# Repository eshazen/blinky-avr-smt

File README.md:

# blinky-avr-smt

## Blinky POV soldering project

This is a soldering practice kit which displays a message in the air
on LEDs when waved back and forth.  

* Programming: https://ohm.bu.edu/~hazen/BlinkyPovAVR/prog/test_prog.html

## Revisions

Revision 5.1 PCB (fall 2023).  See [PCB Documentation](Hardware/avr-smt-44).

* Improve thermal relief on GND/VCC pads
* Change SMT programming connector to thru-hole
* Add pre-programmed message "EPIC"
* Improve error-checking and display on download code
  (blink all LEDs on checksum error)

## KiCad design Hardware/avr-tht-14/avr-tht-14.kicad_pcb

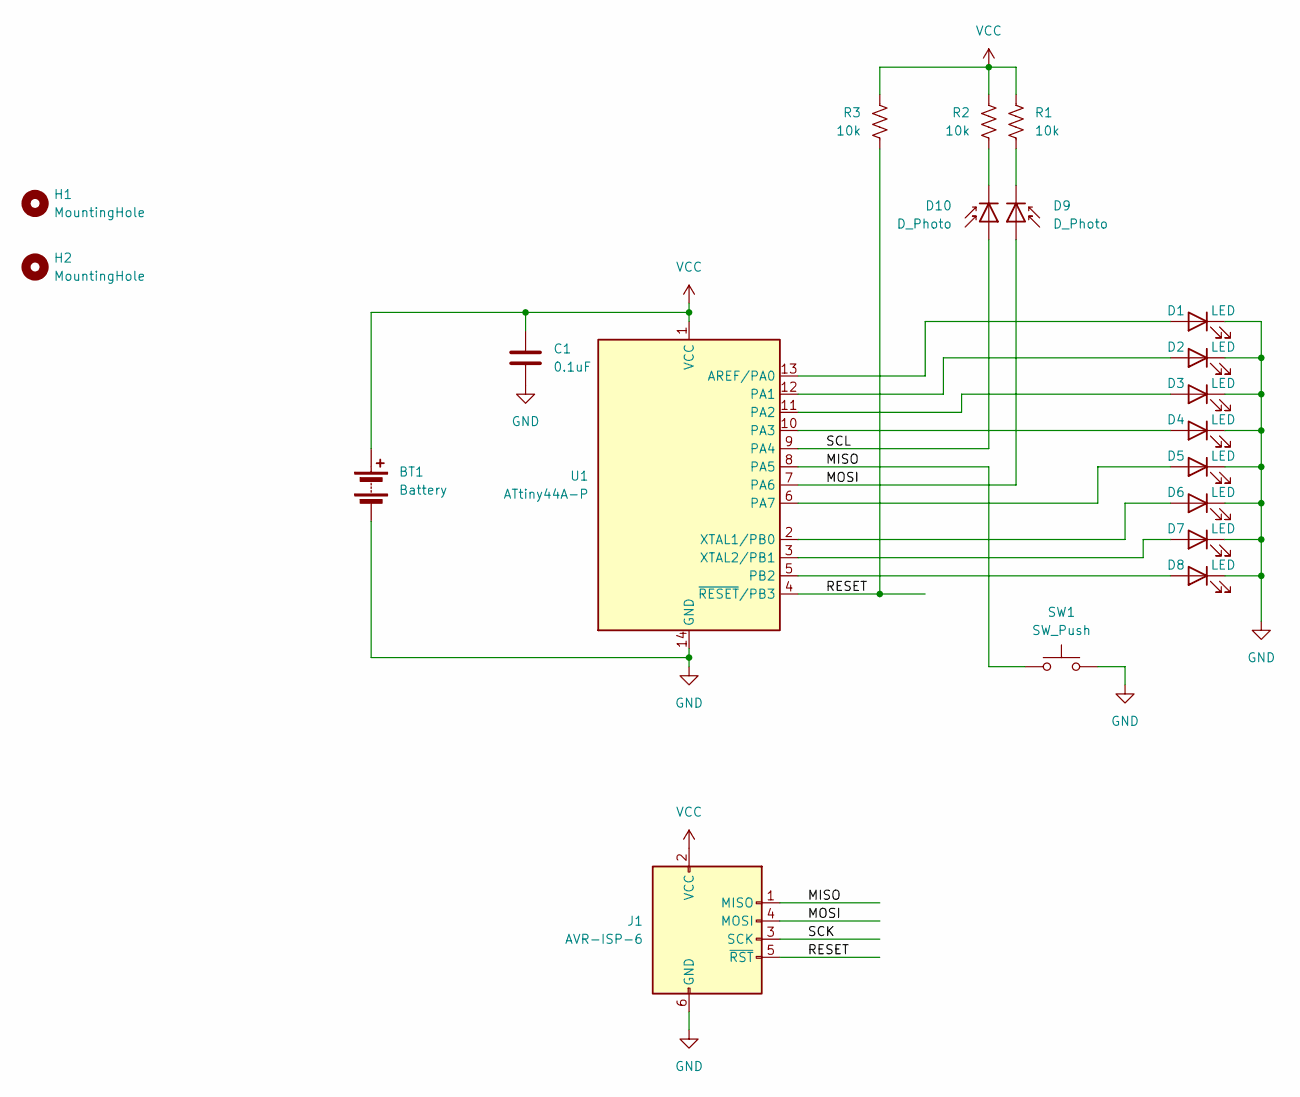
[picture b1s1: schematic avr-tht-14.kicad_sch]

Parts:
BT1: Battery; PinHeader_1x02_P2.54mm_Vertical
C1: 0.1uF; C_Disc_D6.0mm_W2.5mm_P5.00mm
D1, D2, D3, D4, D5, D6, D7, D8: LED; LED_D5.0mm
D9, D10: D_Photo; LED_D3.0mm
H1, H2: MountingHole; MountingHole_4.3mm_M4
J1: AVR-ISP-6; PinHeader_2x03_P2.54mm_Vertical
R1, R2, R3: 10k; R_Axial_DIN0207_L6.3mm_D2.5mm_P10.16mm_Horizontal
SW1: SW_Push; BTN-B3F-1000
U1: ATtiny44A-P; DIP-14_W7.62mm

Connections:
/MISO: J1.1 (MISO), SW1.1, U1.8 (PA5)
/MOSI: D9.2 (A), J1.4 (MOSI), U1.7 (PA6)
/RESET: J1.5 (~RST), R3.2, U1.4 (~RESET/PB3)
/SCK: J1.3 (SCK)
/SCL: D10.2 (A), U1.9 (PA4)
GND: BT1.2 (-), C1.2, D1.1 (K), D2.1 (K), D3.1 (K), D4.1 (K), D5.1 (K), D6.1 (K), D7.1 (K), D8.1 (K), J1.6 (GND), SW1.2, U1.14 (GND)
unnamed: D1.2 (A), U1.13 (AREF/PA0)
unnamed: D2.2 (A), U1.12 (PA1)
unnamed: D3.2 (A), U1.11 (PA2)
unnamed: D4.2 (A), U1.10 (PA3)
unnamed: D5.2 (A), U1.6 (PA7)
unnamed: D6.2 (A), U1.2 (XTAL1/PB0)
unnamed: D7.2 (A), U1.3 (XTAL2/PB1)
unnamed: D8.2 (A), U1.5 (PB2)
unnamed: D9.1 (K), R1.2
unnamed: D10.1 (K), R2.2
VCC: BT1.1 (+), C1.1, J1.2 (VCC), R1.1, R2.1, R3.1, U1.1 (VCC)

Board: 2 copper layers, 20 parts (0 on the bottom side), 16 nets, no tracks yet.

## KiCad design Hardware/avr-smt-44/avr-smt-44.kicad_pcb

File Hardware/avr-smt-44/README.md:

# avr-smt-44

KiCAD design for an SMT version based on ATTiny44/84.
Should be pin/firmware compatible with BlinkyPovAVR4.

## Documentation

* [avr-smt-44.pdf](avr-smt-44.pdf) -- Electrical Schematic
* [avr-smt-44.step](avr-smt-44.step) -- 3D model of assembled board
* [avr-smt-44-Edge_Cuts.pdf](avr-smt-44-Edge_Cuts.pdf) -- Assembly/mechanical drawing
* [avr-smt-44-Edge_Cuts.dxf](avr-smt-44-Edge_Cuts.dxf) -- Assembly/mechanical drawing

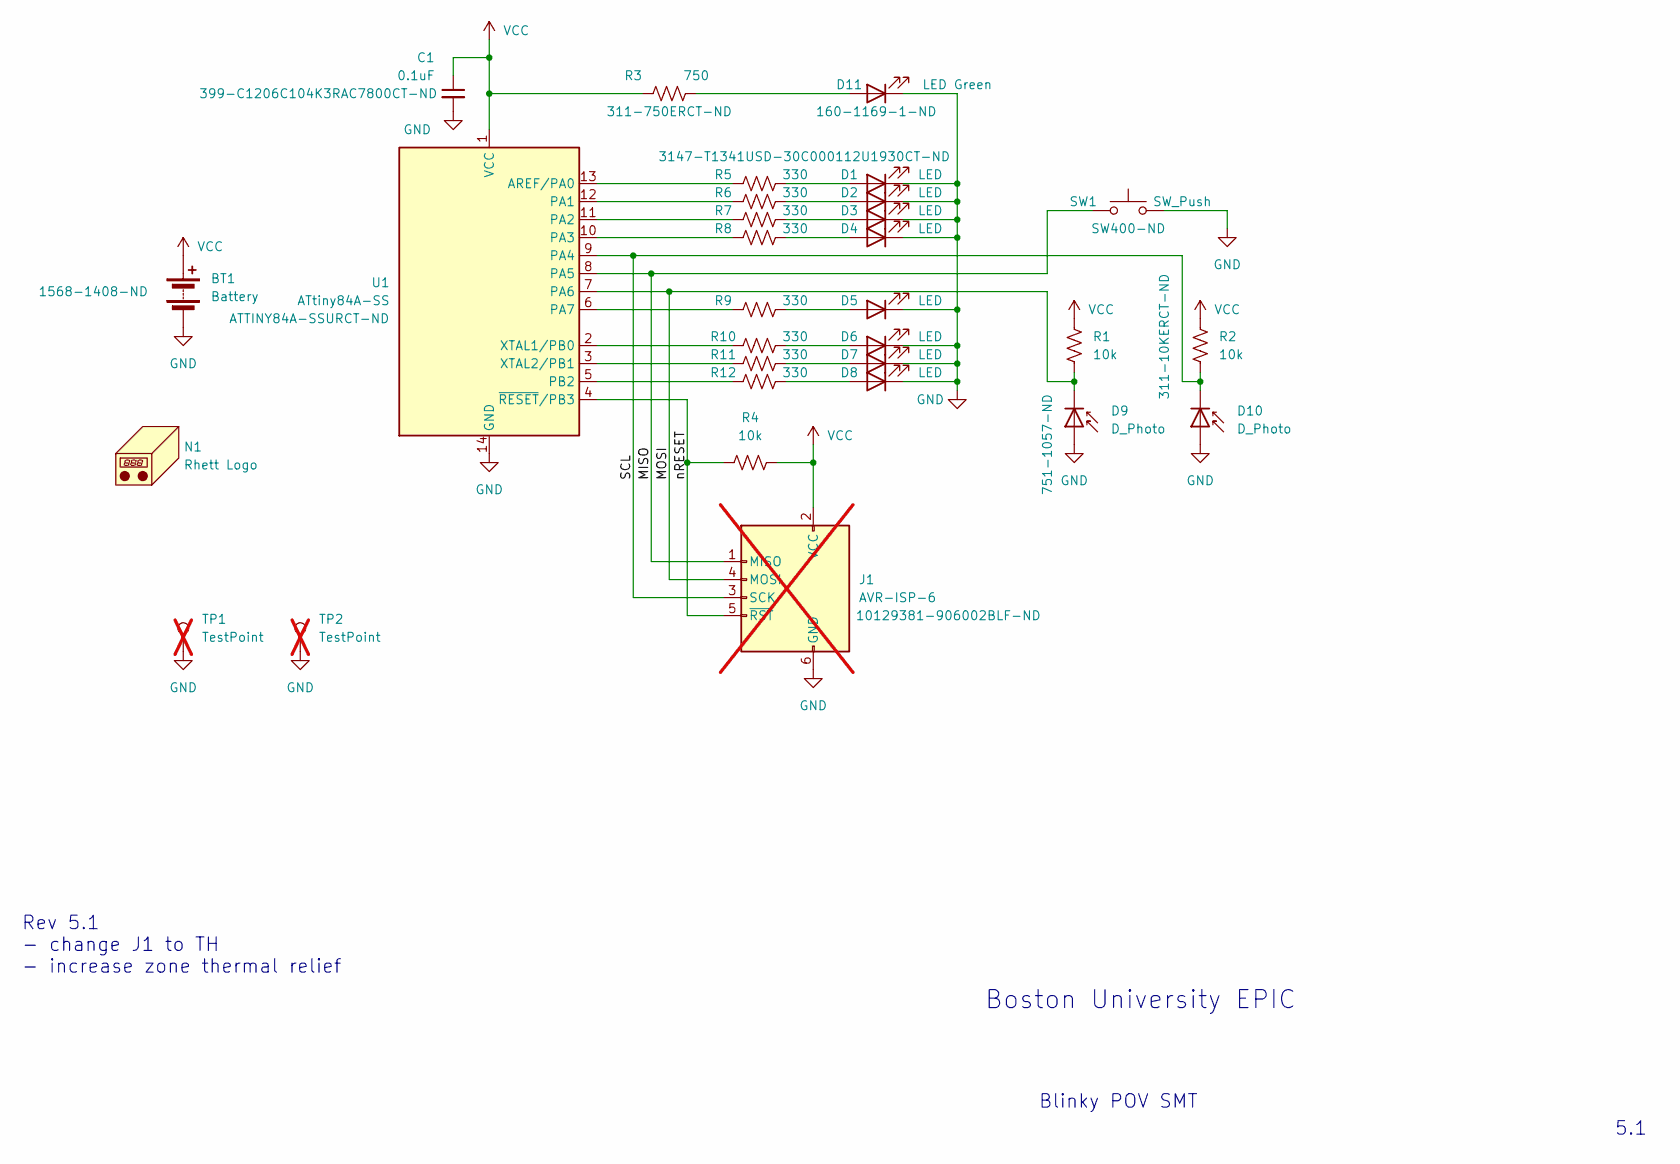
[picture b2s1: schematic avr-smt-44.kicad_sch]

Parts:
BT1: Battery; 2PIN_battery_new2
C1: 0.1uF; C_1206_3216Metric_Pad1.33x1.80mm_HandSolder
D1, D2, D3, D4, D5, D6, D7, D8: LED; LED_1206_3216Metric_Pad1.42x1.75mm_HandSolder
D9, D10: D_Photo; LED_D3.0mm_Horizontal_O3.81mm_Z2.0mm
D11: LED Green; LED_1206_3216Metric_Pad1.42x1.75mm_HandSolder
J1: AVR-ISP-6; PinHeader_2x03_P2.54mm_Vertical; not fitted
N1: Rhett Logo; rhett_logo
R1, R2, R4: 10k; R_1206_3216Metric_Pad1.30x1.75mm_HandSolder
R3: 750; R_1206_3216Metric_Pad1.30x1.75mm_HandSolder
R5, R6, R7, R8, R9, R10, R11, R12: 330; R_1206_3216Metric_Pad1.30x1.75mm_HandSolder
SW1: SW_Push; BTN-B3F-1000
TP1, TP2: TestPoint; TestPoint_Loop_D3.80mm_Drill2.0mm; not fitted
U1: ATtiny84A-SS; SOIC-14_3.9x8.7mm_P1.27mm

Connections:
/MISO: J1.1 (MISO), SW1.1, U1.8 (PA5)
/MOSI: D9.1 (K), J1.4 (MOSI), R1.2, U1.7 (PA6)
/SCL: D10.1 (K), J1.3 (SCK), R2.2, U1.9 (PA4)
/nRESET: J1.5 (~RST), R4.1, U1.4 (~RESET/PB3)
GND: BT1.2 (-), C1.2, D1.1 (K), D2.1 (K), D3.1 (K), D4.1 (K), D5.1 (K), D6.1 (K), D7.1 (K), D8.1 (K), D9.2 (A), D10.2 (A), D11.1 (K), J1.6 (GND), SW1.2, TP1.1, TP2.1, U1.14 (GND)
unnamed: D1.2 (A), R5.2
unnamed: D2.2 (A), R6.2
unnamed: D3.2 (A), R7.2
unnamed: D4.2 (A), R8.2
unnamed: D5.2 (A), R9.2
unnamed: D6.2 (A), R10.2
unnamed: D7.2 (A), R11.2
unnamed: D8.2 (A), R12.2
unnamed: D11.2 (A), R3.2
unnamed: R5.1, U1.13 (AREF/PA0)
unnamed: R6.1, U1.12 (PA1)
unnamed: R7.1, U1.11 (PA2)
unnamed: R8.1, U1.10 (PA3)
unnamed: R9.1, U1.6 (PA7)
unnamed: R12.1, U1.5 (PB2)
unnamed: R10.1, U1.2 (XTAL1/PB0)
unnamed: R11.1, U1.3 (XTAL2/PB1)
VCC: BT1.1 (+), C1.1, J1.2 (VCC), R1.1, R2.1, R3.1, R4.2, U1.1 (VCC)

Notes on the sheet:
Rev 5.1 - change J1 to TH - increase zone thermal relief
5.1
Boston University EPIC
Blinky POV SMT

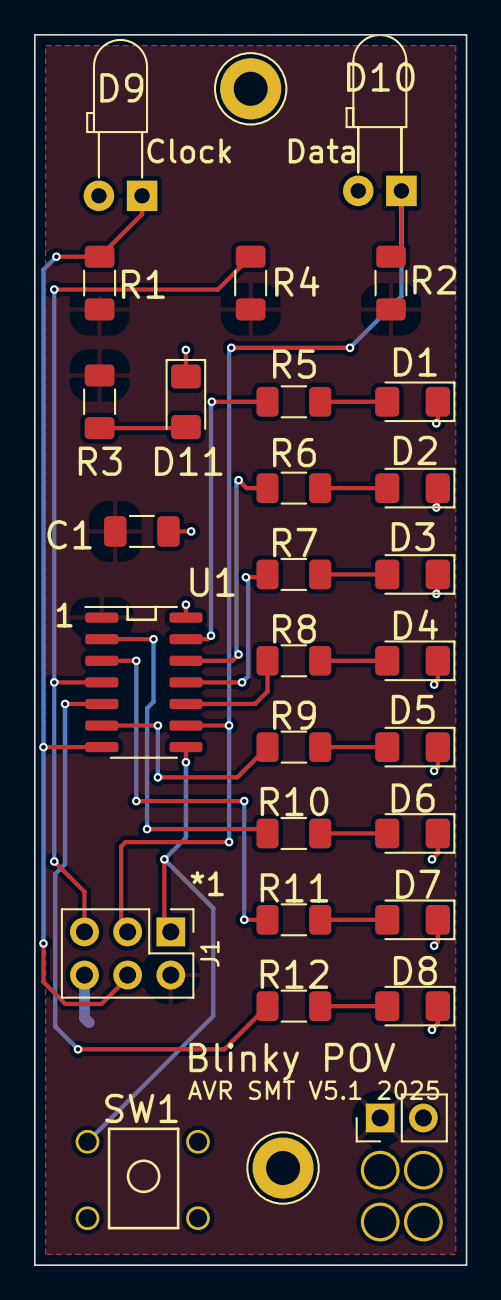
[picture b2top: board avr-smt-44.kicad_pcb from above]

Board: 2 copper layers, 25.4 x 72.4 mm, 31 parts (1 on the bottom side), 23 nets.

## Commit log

2023-09-11 readme
2023-09-16 SMT 44 version, placement done
2023-09-16 Add series R, re-place
2023-09-16 V5 for submit
2023-10-10 assembly docs
2023-10-10 ported firmware working
2023-10-10 photos
2023-10-10 instructions and readmes
2023-10-12 Add programming code
2023-10-21 add pdf schematic
2023-10-24 instructions
2023-11-06 clean up lock
2023-11-06 update docs
2023-11-06 update PDFs
2023-11-10 instructions edit
2023-11-11 V5.1 PCB, notes
2023-11-13 Add power-up reset of EEPROM on button press
2023-11-16 V5.1 as built
2024-01-19 change to AVR programmer, update comments
2024-01-19 tweak programming page
2024-01-19 fix up 3D model, update instructions
2024-02-08 updated instructions and assy dwg for 2/12 class
2024-04-23 update readmes
2024-11-13 add some docs
2024-11-13 Tweak documentation
2025-05-15 re-spin 2025
2025-05-19 v5.1 2025 edition
2025-09-22 update instructions
2025-12-09 case2
2025-12-15 New THT version
